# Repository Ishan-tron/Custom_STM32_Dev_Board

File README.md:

# Custom_STM32_Dev_Board
STM32 PCB Designed in KiCAD

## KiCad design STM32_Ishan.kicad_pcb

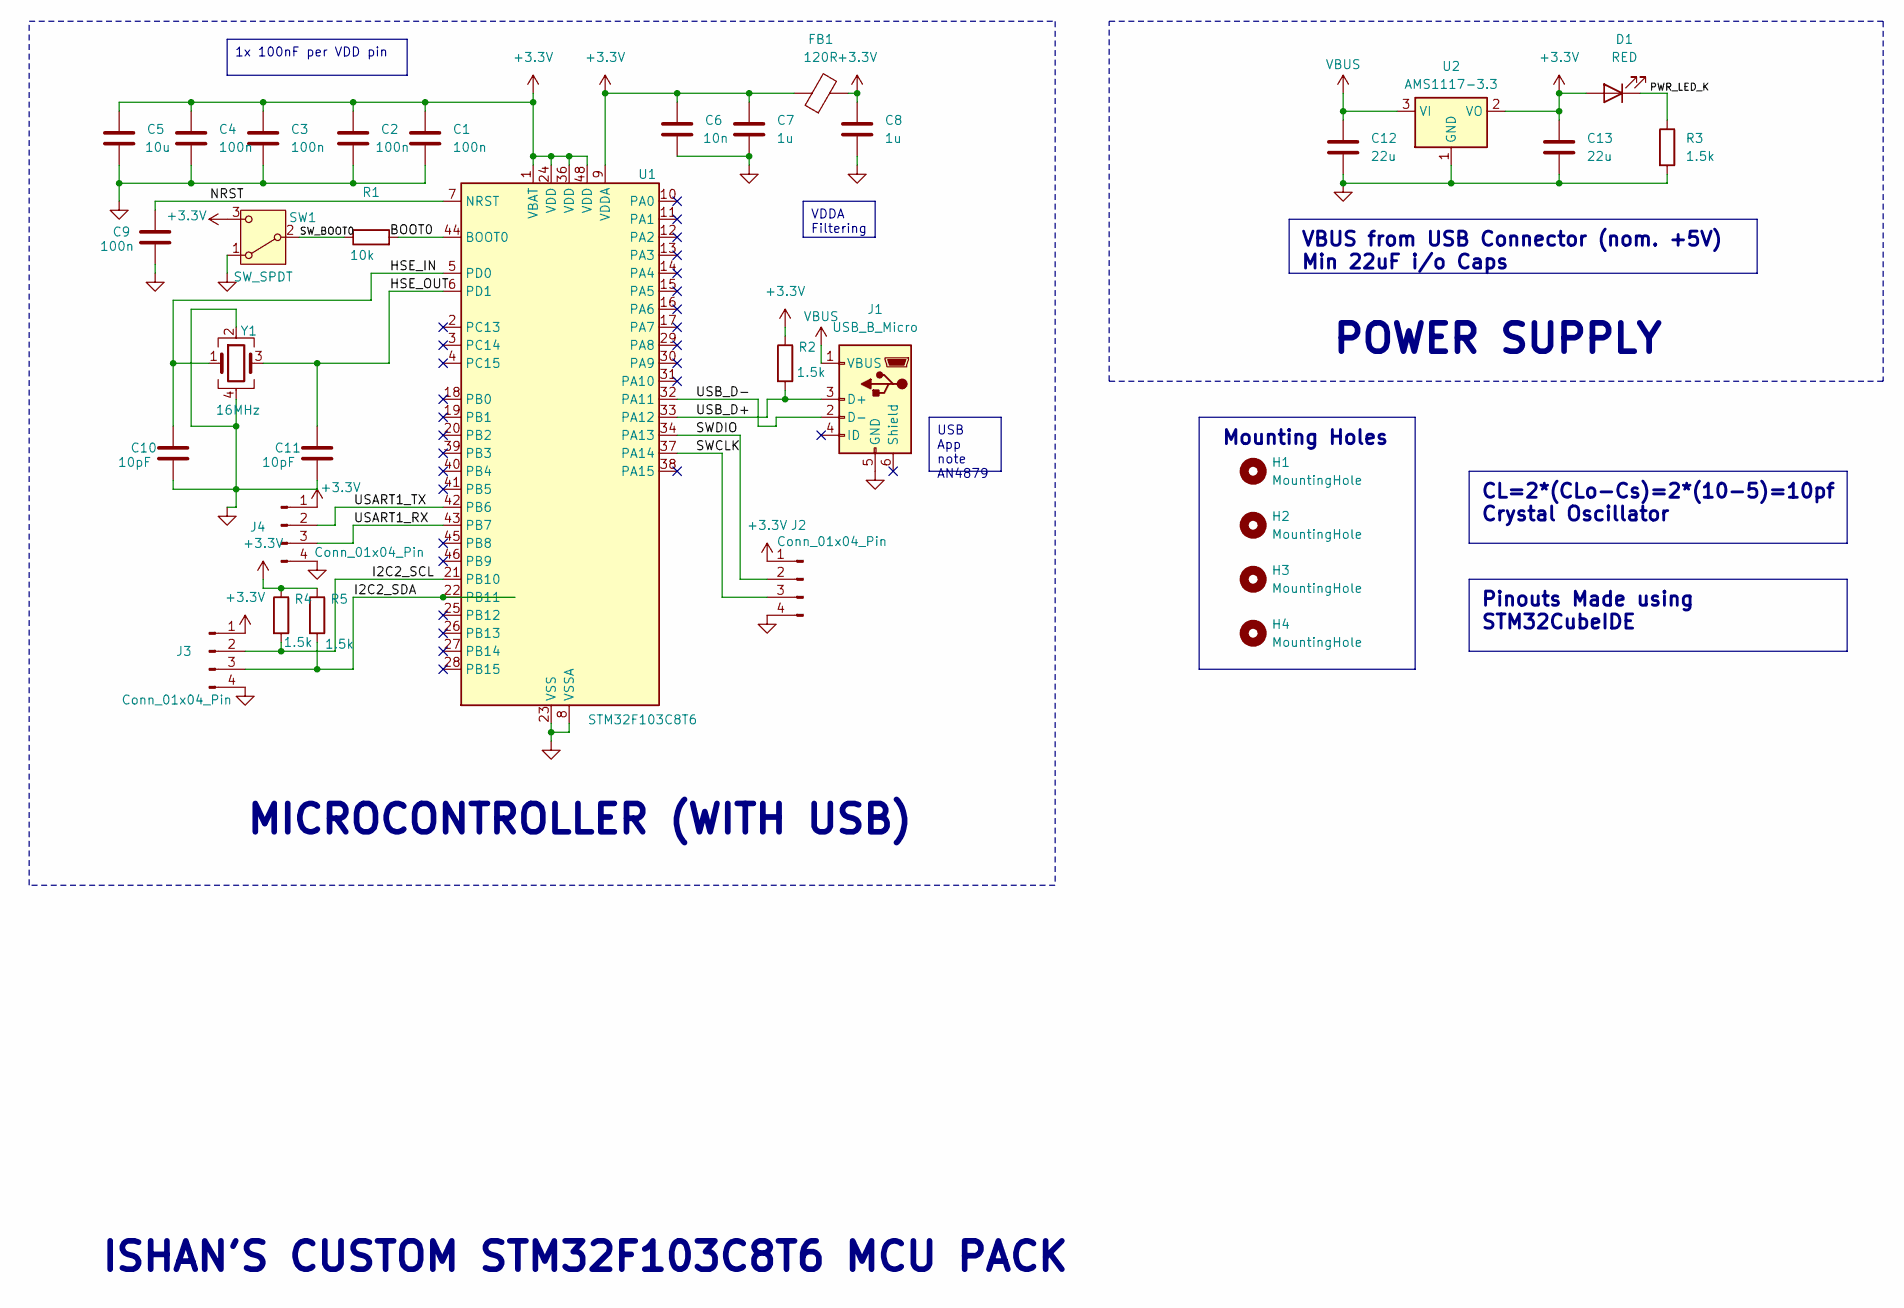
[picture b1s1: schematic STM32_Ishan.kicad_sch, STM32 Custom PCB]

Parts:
C1, C2, C3, C4, C9: 100n; C_0402_1005Metric
C5: 10u; C_0603_1608Metric
C6: 10n; C_0402_1005Metric
C7, C8: 1u; C_0402_1005Metric
C10, C11: 10pF; C_0402_1005Metric
C12, C13: 22u; C_0805_2012Metric
D1: RED; LED_0603_1608Metric
FB1: 120R; L_0201_0603Metric
H1, H2, H3, H4: MountingHole; MountingHole_2.2mm_M2
J1: USB_B_Micro; USB_Micro-B_Wuerth_629105150521
J2, J3, J4: Conn_01x04_Pin; PinHeader_1x04_P2.54mm_Vertical
R1: 10k; R_01005_0402Metric
R2, R3, R4, R5: 1.5k; R_01005_0402Metric
SW1: SW_SPDT; SW_SPDT_PCM12
U1: STM32F103C8T6; LQFP-48_7x7mm_P0.5mm
U2: AMS1117-3.3; SOT-223-3_TabPin2
Y1: 16MHz; Crystal_SMD_3225-4Pin_3.2x2.5mm

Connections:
+3.3V: C1.1, C2.1, C3.1, C4.1, C5.1, C6.1, C7.1, C8.1, C13.1, D1.2 (A), FB1.1, FB1.2, J2.1, J3.1, J4.1, R2.1, R4.1, R5.1, SW1.3 (C), U1.1 (VBAT), U1.9 (VDDA), U1.24 (VDD), U1.36 (VDD), U1.48 (VDD), U2.2 (VO)
/HSE_IN: C10.1, U1.5 (PD0), Y1.1
/HSE_OUT: C11.1, U1.6 (PD1), Y1.3
/I2C2_SCL: J3.2, R4.2, U1.21 (PB10)
/I2C2_SDA: J3.3, R5.2, U1.22 (PB11)
/NRST: C9.1, U1.7 (NRST)
/PWR_LED_K: D1.1 (K), R3.1
/SWCLK: J2.3, U1.37 (PA14)
/SWDIO: J2.2, U1.34 (PA13)
/SW_BOOT0: R1.1, SW1.2 (B)
/USART1_RX: J4.3, U1.43 (PB7)
/USART1_TX: J4.2, U1.42 (PB6)
/USB_D+: J1.3 (D+), R2.2, U1.33 (PA12)
/USB_D-: J1.2 (D-), U1.32 (PA11)
GND: C1.2, C2.2, C3.2, C4.2, C5.2, C6.2, C7.2, C8.2, C9.2, C10.2, C11.2, C12.2, C13.2, J1.5 (GND), J2.4, J3.4, J4.4, R3.2, SW1.1 (A), U1.8 (VSSA), U1.23 (VSS), U1.35 (VSS), U1.47 (VSS), U2.1 (GND), Y1.2, Y1.4
unnamed: R1.2, U1.44 (BOOT0)
VBUS: C12.1, J1.1 (VBUS), U2.3 (VI)

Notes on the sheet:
VDDA Filtering
USB App note AN4879
1x 100nF per VDD pin
Pinouts Made using STM32CubeIDE
VBUS from USB Connector (nom. +5V) Min 22uF i/o Caps
CL=2*(CLo-Cs)=2*(10-5)=10pf Crystal Oscillator
ISHAN'S CUSTOM STM32F103C8T6 MCU PACK
POWER SUPPLY
Mounting Holes
MICROCONTROLLER (WITH USB)

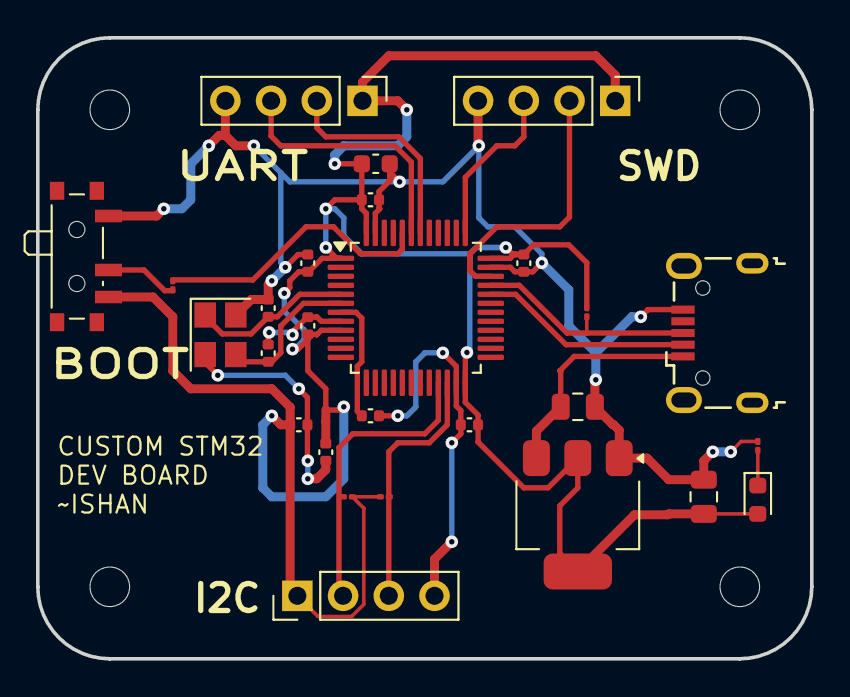
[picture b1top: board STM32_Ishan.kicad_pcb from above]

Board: 2 copper layers, 43.0 x 34.5 mm, 32 parts (0 on the bottom side), 17 nets.
